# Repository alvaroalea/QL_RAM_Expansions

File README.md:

# SINCLAIR QL RAM Expansion Boards

## THIS IS THE DEVEL REPOSITORY, USE AT YOUR OWN RISK

(C) 2022-2026 Alvaro Alea Fernandez and others

If no license is specify in each folder, are under: CERN Open Hardware Licence Version 2 - Strongly Reciprocal

https://ohwr.org/cern_ohl_s_v2.txt

This reporsitory contains severals design of RAM expansion boards for the Sinclair QL, some of them area new design, and other are reverse enginiered of products seld in the 80's for the sinclair QL:

## QL_external_ram_896Kb

New design in 2026, based on qubide card of liont, https://hackaday.io/project/183490-qubide-clone-with-640k-or-704k-ram-upgrade-for-ql

Include a 1Mbyte StaticRam in a very small board with pass-through. This is the prefered design if you are new to the Sinclair QL

## qlexternal512kram_MIX

My old 2022 design, based on qubide card of Jose Leandro and work of McLeod Ideafix, using a 512Kb StaticRam in a very small board with pass-through. two of this board can be stacked to achive the 892Kb of RAM that is the maximun possible on a Sinclair QL

## QL_Internal_512Kb_SRAM

This is a clone of a model sell in ebay of a internal expansion RAM, similar to my internal 512Kb card, it fit between the 68008 and the mainboard of the QL

## QL_2560RAM_ROM

A board saw in theqlforum that include 256Kb of RAM and an chip of ROM, ideally to incorporate a ToolKit to the RAM expansion

## QL_Miracle_Trump_RAM

A board saw in theqlforum, this board include 2x256Kb of Dinamic RAM, for use with normal QL or QL with Trump Card 0Kb.

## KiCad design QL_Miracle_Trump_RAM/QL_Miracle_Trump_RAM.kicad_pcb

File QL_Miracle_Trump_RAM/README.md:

# Miracle's 256-512Kb ExpandRam board for Sinclair QL

## THIS HAS NOT BEEN TESTED, USE UNDER YOU RESPONSABILITY

(C) 2026 Alvaro Alea Fernandez

License under: CERN Open Hardware Licence Version 2 - Strongly Reciprocal

https://ohwr.org/cern_ohl_s_v2.txt

##Instructions

### COMPONENTE REQUIERED

8 or 16  41256 RAM chips 120 to 150nS SPEED.

If fitting 8 RAMS (256K) the row closest to the edge connector should be used.

Pin One of the RAM chips is furthest from above edge connector.

CARE ELECTRONICS

800 St Albans RD

GARSTON

WATFORD

HERTS        TEL 0923 672102

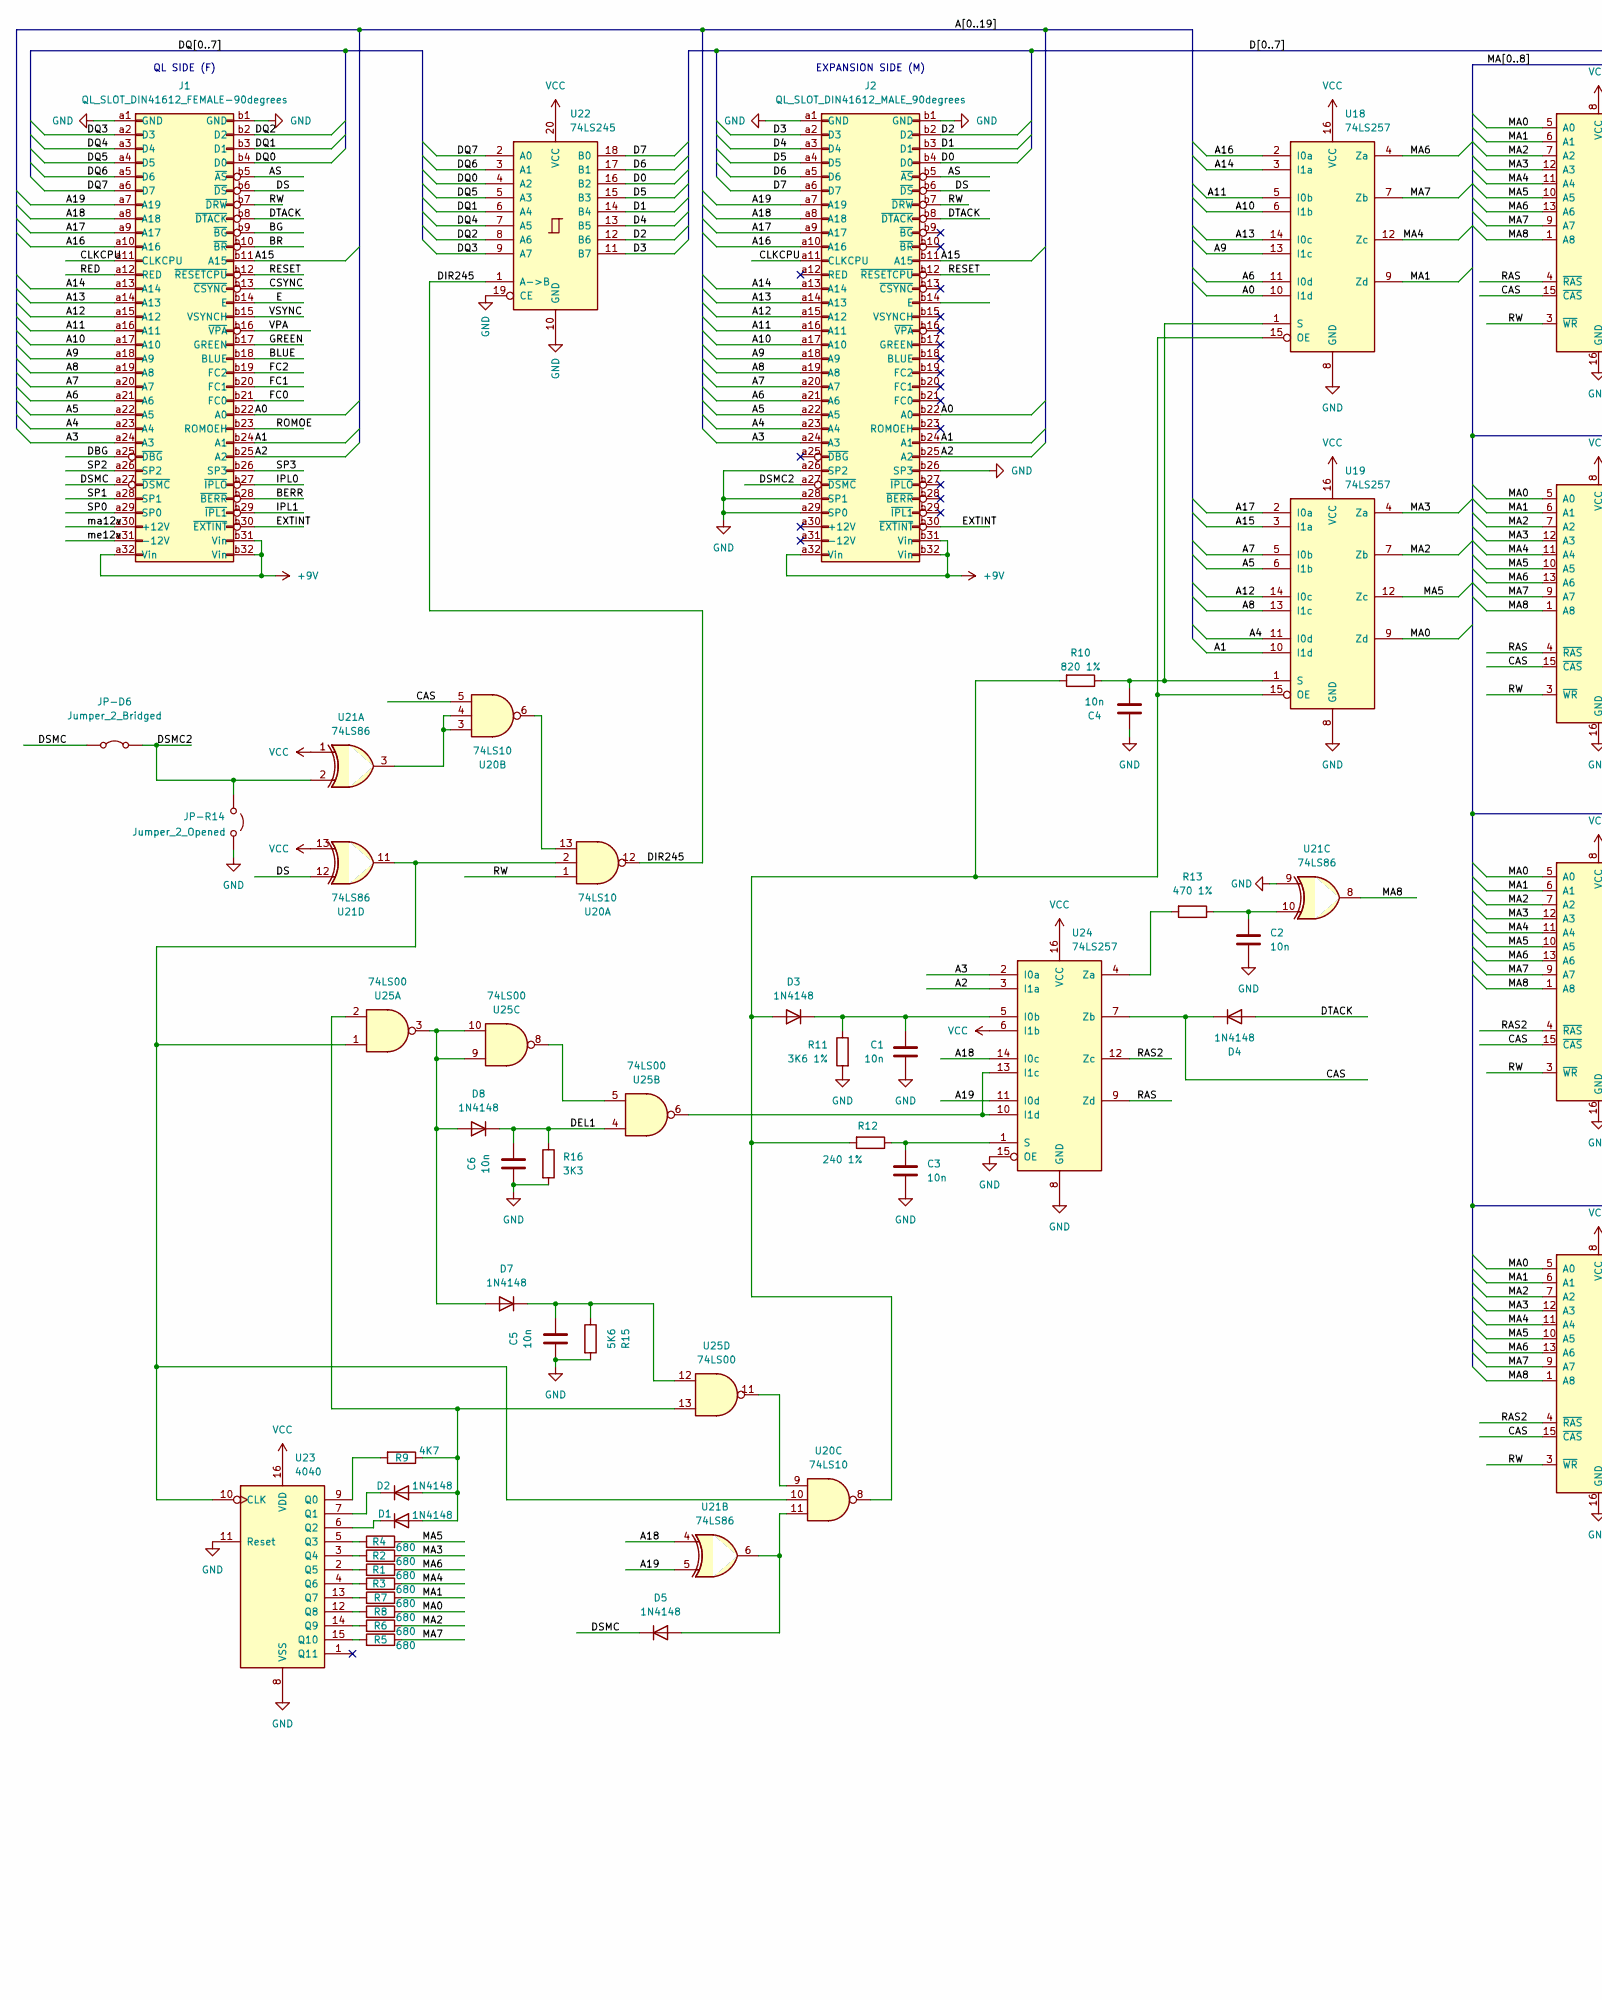
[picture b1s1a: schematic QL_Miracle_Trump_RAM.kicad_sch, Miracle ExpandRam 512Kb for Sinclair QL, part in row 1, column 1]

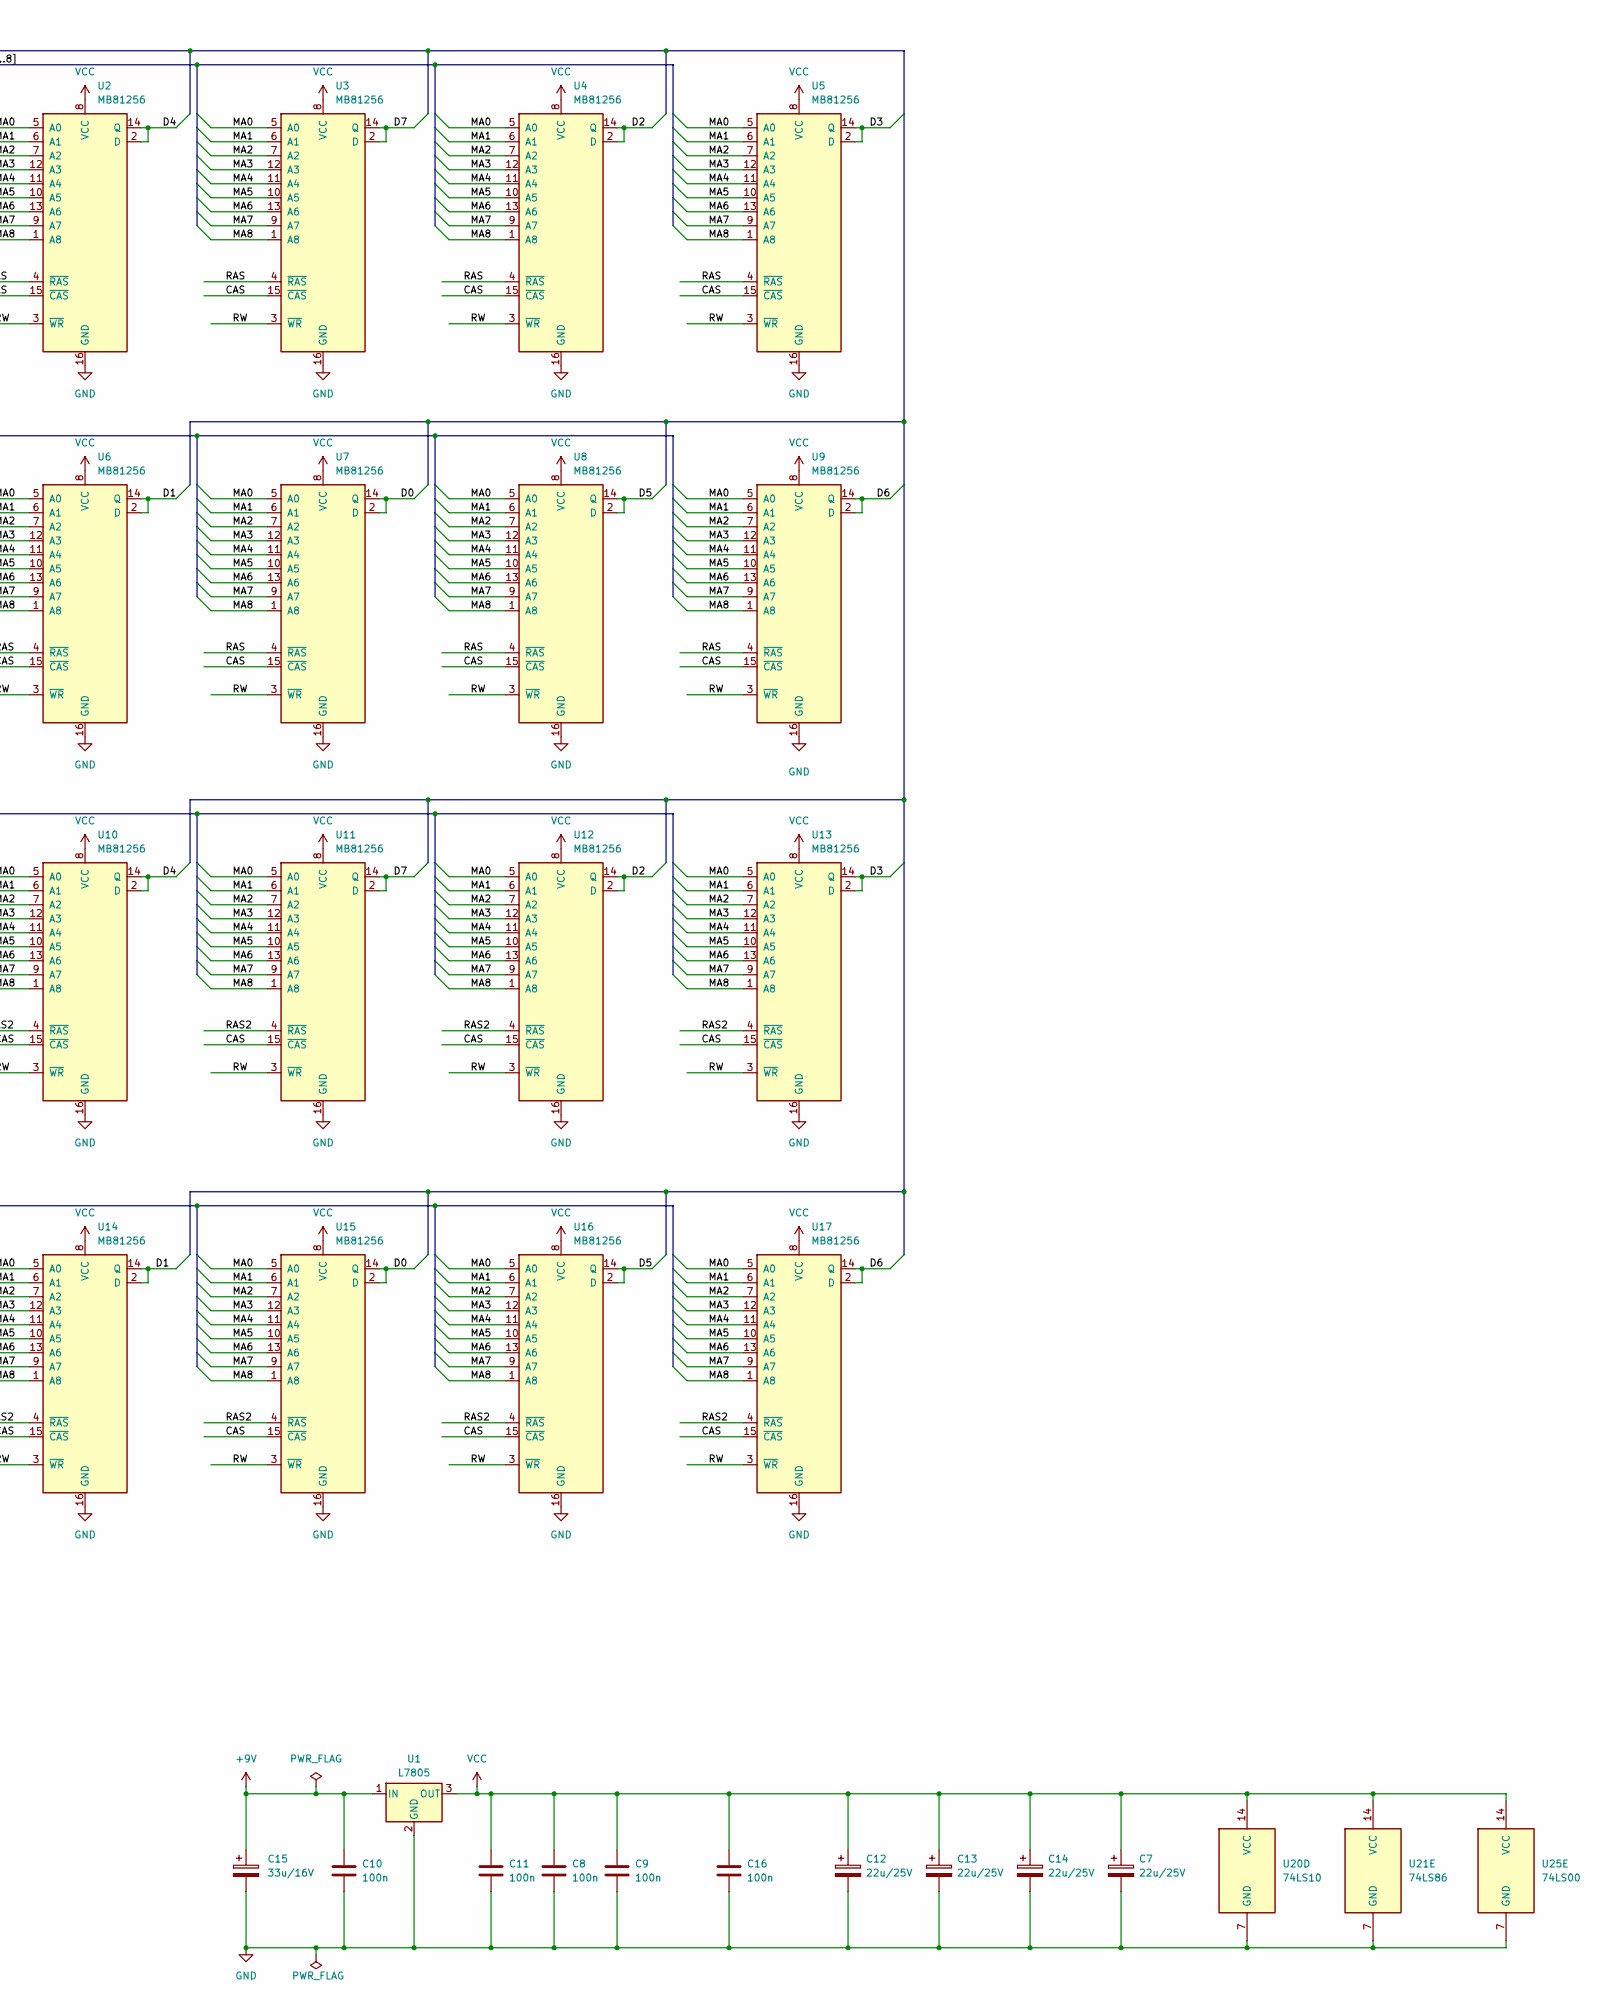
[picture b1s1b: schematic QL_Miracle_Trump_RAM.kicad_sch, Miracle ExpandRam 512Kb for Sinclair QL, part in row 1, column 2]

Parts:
C1, C2, C3, C4, C5, C6: 10n; C_Disc_D4.3mm_W1.9mm_P5.00mm
C7, C12, C13, C14: 22u/25V; CP_Radial_D8.0mm_P5.00mm
C8, C9, C10, C11, C16: 100n; C_Disc_D4.3mm_W1.9mm_P5.00mm
C15: 33u/16V; CP_Axial_L11.0mm_D5.0mm_P18.00mm_Horizontal
D1, D2, D3, D4, D5, D7, D8: 1N4148; D_DO-35_SOD27_P10.16mm_Horizontal
J1: QL_SLOT_DIN41612_FEMALE-90degrees; DIN41612_B_2x32_Female_Horizontal_THT
J2: QL_SLOT_DIN41612_MALE_90degrees; DIN41612_B_2x32_Male_Horizontal_THT
JP-D6: Jumper_2_Bridged; Jumper_P10.16mm_Horizontal
JP-R14: Jumper_2_Opened; Jumper_P10.16mm_Horizontal
R1, R2, R3, R4, R5, R6, R7, R8: 680; R_Axial_DIN0207_L6.3mm_D2.5mm_P10.16mm_Horizontal
R9: 4K7; R_Axial_DIN0207_L6.3mm_D2.5mm_P10.16mm_Horizontal
R10: 820 1%; R_Axial_DIN0207_L6.3mm_D2.5mm_P10.16mm_Horizontal
R11: 3K6 1%; R_Axial_DIN0207_L6.3mm_D2.5mm_P10.16mm_Horizontal
R12: 240 1%; R_Axial_DIN0207_L6.3mm_D2.5mm_P10.16mm_Horizontal
R13: 470 1%; R_Axial_DIN0207_L6.3mm_D2.5mm_P10.16mm_Horizontal
R15: 5K6; R_Axial_DIN0207_L6.3mm_D2.5mm_P10.16mm_Horizontal
R16: 3K3; R_Axial_DIN0207_L6.3mm_D2.5mm_P10.16mm_Horizontal
U1: L7805; TO-220-3_Horizontal_TabDown
U2, U3, U4, U5, U6, U7, U8, U9, U10, U11, U12, U13, U14, U15, U16, U17: MB81256; DIP-16_W7.62mm
U18, U19, U24: 74LS257; DIP-16_W7.62mm
U20: 74LS10; DIP-14_W7.62mm
U21: 74LS86; DIP-14_W7.62mm
U22: 74LS245; DIP-20_W7.62mm
U23: 4040; DIP-16_W7.62mm
U25: 74LS00; DIP-14_W7.62mm

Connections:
+9V: C10.1, C15.1, J1.a32 (Vin), J1.b31 (Vin), J1.b32 (Vin), J2.a32 (Vin), J2.b31 (Vin), J2.b32 (Vin), U1.1 (IN)
/A0: J1.b22 (A0), J2.b22 (A0), U18.10 (I1d)
/A1: J1.b24 (A1), J2.b24 (A1), U19.10 (I1d)
/A2: J1.b25 (A2), J2.b25 (A2), U24.3 (I1a)
/A3: J1.a24 (A3), J2.a24 (A3), U24.2 (I0a)
/A4: J1.a23 (A4), J2.a23 (A4), U19.11 (I0d)
/A5: J1.a22 (A5), J2.a22 (A5), U19.6 (I1b)
/A6: J1.a21 (A6), J2.a21 (A6), U18.11 (I0d)
/A7: J1.a20 (A7), J2.a20 (A7), U19.5 (I0b)
/A8: J1.a19 (A8), J2.a19 (A8), U19.13 (I1c)
/A9: J1.a18 (A9), J2.a18 (A9), U18.13 (I1c)
/A10: J1.a17 (A10), J2.a17 (A10), U18.6 (I1b)
/A11: J1.a16 (A11), J2.a16 (A11), U18.5 (I0b)
/A12: J1.a15 (A12), J2.a15 (A12), U19.14 (I0c)
/A13: J1.a14 (A13), J2.a14 (A13), U18.14 (I0c)
/A14: J1.a13 (A14), J2.a13 (A14), U18.3 (I1a)
/A15: J1.b11 (A15), J2.b11 (A15), U19.3 (I1a)
/A16: J1.a10 (A16), J2.a10 (A16), U18.2 (I0a)
/A17: J1.a9 (A17), J2.a9 (A17), U19.2 (I0a)
/A18: J1.a8 (A18), J2.a8 (A18), U21.4, U24.14 (I0c)
/A19: J1.a7 (A19), J2.a7 (A19), U21.5, U24.11 (I0d)
/AS: J1.b5 (~AS), J2.b5 (~AS)
/BERR: J1.b28 (~BERR)
/BG: J1.b9 (~BG)
/BLUE: J1.b18 (BLUE)
/BR: J1.b10 (~BR)
/CAS: D4.1 (K), U2.15 (~CAS), U3.15 (~CAS), U4.15 (~CAS), U5.15 (~CAS), U6.15 (~CAS), U7.15 (~CAS), U8.15 (~CAS), U9.15 (~CAS), U10.15 (~CAS), U11.15 (~CAS), U12.15 (~CAS), U13.15 (~CAS), U14.15 (~CAS), U15.15 (~CAS), U16.15 (~CAS), U17.15 (~CAS), U20.5, U24.7 (Zb)
/CLKCPU: J1.a11 (CLKCPU), J2.a11 (CLKCPU)
/CSYNC: J1.b13 (~CSYNC)
/D0: J2.b4 (D0), U7.2 (D), U7.14 (Q), U15.2 (D), U15.14 (Q), U22.16 (B2)
/D1: J2.b3 (D1), U6.2 (D), U6.14 (Q), U14.2 (D), U14.14 (Q), U22.14 (B4)
/D2: J2.b2 (D2), U4.2 (D), U4.14 (Q), U12.2 (D), U12.14 (Q), U22.12 (B6)
/D3: J2.a2 (D3), U5.2 (D), U5.14 (Q), U13.2 (D), U13.14 (Q), U22.11 (B7)
/D4: J2.a3 (D4), U2.2 (D), U2.14 (Q), U10.2 (D), U10.14 (Q), U22.13 (B5)
/D5: J2.a4 (D5), U8.2 (D), U8.14 (Q), U16.2 (D), U16.14 (Q), U22.15 (B3)
/D6: J2.a5 (D6), U9.2 (D), U9.14 (Q), U17.2 (D), U17.14 (Q), U22.17 (B1)
/D7: J2.a6 (D7), U3.2 (D), U3.14 (Q), U11.2 (D), U11.14 (Q), U22.18 (B0)
/DBG: J1.a25 (~DBG)
/DEL1: C6.1, D8.1 (K), R16.1, U25.4
/DIR245: U20.12, U22.1 (A->B)
/DQ0: J1.b4 (D0), U22.4 (A2)
/DQ1: J1.b3 (D1), U22.6 (A4)
/DQ2: J1.b2 (D2), U22.8 (A6)
/DQ3: J1.a2 (D3), U22.9 (A7)
/DQ4: J1.a3 (D4), U22.7 (A5)
/DQ5: J1.a4 (D5), U22.5 (A3)
/DQ6: J1.a5 (D6), U22.3 (A1)
/DQ7: J1.a6 (D7), U22.2 (A0)
/DS: J1.b6 (~DS), J2.b6 (~DS), U21.12
/DSMC: D5.1 (K), J1.a27 (~DSMC), JP-D6.1 (A)
/DSMC2: J2.a27 (~DSMC), JP-D6.2 (B), JP-R14.1 (A), U21.2
/DTACK: D4.2 (A), J1.b8 (~DTACK), J2.b8 (~DTACK)
/E: J1.b14 (E)
/EXTINT: J1.b30 (~EXTINT), J2.b30 (~EXTINT)
/FC0: J1.b21 (FC0)
/FC1: J1.b20 (FC1)
/FC2: J1.b19 (FC2)
/GREEN: J1.b17 (GREEN)
/IPL0: J1.b27 (~IPLO)
/IPL1: J1.b29 (~IPL1)
/MA0: R8.1, U2.5 (A0), U3.5 (A0), U4.5 (A0), U5.5 (A0), U6.5 (A0), U7.5 (A0), U8.5 (A0), U9.5 (A0), U10.5 (A0), U11.5 (A0), U12.5 (A0), U13.5 (A0), U14.5 (A0), U15.5 (A0), U16.5 (A0), U17.5 (A0), U19.9 (Zd)
/MA1: R7.1, U2.6 (A1), U3.6 (A1), U4.6 (A1), U5.6 (A1), U6.6 (A1), U7.6 (A1), U8.6 (A1), U9.6 (A1), U10.6 (A1), U11.6 (A1), U12.6 (A1), U13.6 (A1), U14.6 (A1), U15.6 (A1), U16.6 (A1), U17.6 (A1), U18.9 (Zd)
/MA2: R6.1, U2.7 (A2), U3.7 (A2), U4.7 (A2), U5.7 (A2), U6.7 (A2), U7.7 (A2), U8.7 (A2), U9.7 (A2), U10.7 (A2), U11.7 (A2), U12.7 (A2), U13.7 (A2), U14.7 (A2), U15.7 (A2), U16.7 (A2), U17.7 (A2), U19.7 (Zb)
/MA3: R2.1, U2.12 (A3), U3.12 (A3), U4.12 (A3), U5.12 (A3), U6.12 (A3), U7.12 (A3), U8.12 (A3), U9.12 (A3), U10.12 (A3), U11.12 (A3), U12.12 (A3), U13.12 (A3), U14.12 (A3), U15.12 (A3), U16.12 (A3), U17.12 (A3), U19.4 (Za)
/MA4: R3.1, U2.11 (A4), U3.11 (A4), U4.11 (A4), U5.11 (A4), U6.11 (A4), U7.11 (A4), U8.11 (A4), U9.11 (A4), U10.11 (A4), U11.11 (A4), U12.11 (A4), U13.11 (A4), U14.11 (A4), U15.11 (A4), U16.11 (A4), U17.11 (A4), U18.12 (Zc)
/MA5: R4.1, U2.10 (A5), U3.10 (A5), U4.10 (A5), U5.10 (A5), U6.10 (A5), U7.10 (A5), U8.10 (A5), U9.10 (A5), U10.10 (A5), U11.10 (A5), U12.10 (A5), U13.10 (A5), U14.10 (A5), U15.10 (A5), U16.10 (A5), U17.10 (A5), U19.12 (Zc)
/MA6: R1.1, U2.13 (A6), U3.13 (A6), U4.13 (A6), U5.13 (A6), U6.13 (A6), U7.13 (A6), U8.13 (A6), U9.13 (A6), U10.13 (A6), U11.13 (A6), U12.13 (A6), U13.13 (A6), U14.13 (A6), U15.13 (A6), U16.13 (A6), U17.13 (A6), U18.4 (Za)
/MA7: R5.1, U2.9 (A7), U3.9 (A7), U4.9 (A7), U5.9 (A7), U6.9 (A7), U7.9 (A7), U8.9 (A7), U9.9 (A7), U10.9 (A7), U11.9 (A7), U12.9 (A7), U13.9 (A7), U14.9 (A7), U15.9 (A7), U16.9 (A7), U17.9 (A7), U18.7 (Zb)
/MA8: U2.1 (A8), U3.1 (A8), U4.1 (A8), U5.1 (A8), U6.1 (A8), U7.1 (A8), U8.1 (A8), U9.1 (A8), U10.1 (A8), U11.1 (A8), U12.1 (A8), U13.1 (A8), U14.1 (A8), U15.1 (A8), U16.1 (A8), U17.1 (A8), U21.8
/RAS: U2.4 (~RAS), U3.4 (~RAS), U4.4 (~RAS), U5.4 (~RAS), U6.4 (~RAS), U7.4 (~RAS), U8.4 (~RAS), U9.4 (~RAS), U24.9 (Zd)
/RAS2: U10.4 (~RAS), U11.4 (~RAS), U12.4 (~RAS), U13.4 (~RAS), U14.4 (~RAS), U15.4 (~RAS), U16.4 (~RAS), U17.4 (~RAS), U24.12 (Zc)
/RED: J1.a12 (RED)
/RESET: J1.b12 (~RESETCPU), J2.b12 (~RESETCPU)
/ROMOE: J1.b23 (ROMOEH)
/RW: J1.b7 (~DRW), J2.b7 (~DRW), U2.3 (~WR), U3.3 (~WR), U4.3 (~WR), U5.3 (~WR), U6.3 (~WR), U7.3 (~WR), U8.3 (~WR), U9.3 (~WR), U10.3 (~WR), U11.3 (~WR), U12.3 (~WR), U13.3 (~WR), U14.3 (~WR), U15.3 (~WR), U16.3 (~WR), U17.3 (~WR), U20.1
/SP0: J1.a29 (SP0)
/SP1: J1.a28 (SP1)
/SP2: J1.a26 (SP2)
/SP3: J1.b26 (SP3)
/VPA: J1.b16 (~VPA)
/VSYNC: J1.b15 (VSYNCH)
/ma12v: J1.a30 (+12V)
/me12v: J1.a31 (-12V)
GND: C1.2, C2.2, C3.1, C4.2, C5.2, C6.2, C7.2, C8.2, C9.2, C10.2, C11.2, C12.2, C13.2, C14.2, C15.2, C16.2, J1.a1 (GND), J1.b1 (GND), J2.a1 (GND), J2.a26 (SP2), J2.a28 (SP1), J2.a29 (SP0), J2.b1 (GND), J2.b26 (SP3), JP-R14.2 (B), R11.2, R15.2, R16.2, U1.2 (GND), U2.16 (GND), U3.16 (GND), U4.16 (GND), U5.16 (GND), U6.16 (GND), U7.16 (GND), U8.16 (GND), U9.16 (GND), U10.16 (GND), U11.16 (GND), U12.16 (GND), U13.16 (GND), U14.16 (GND), U15.16 (GND), U16.16 (GND), U17.16 (GND), U18.8 (GND), U19.8 (GND), U20.7 (GND), U21.7 (GND), U21.9, U22.10 (GND), U22.19 (CE), U23.8 (VSS), U23.11 (Reset), U24.8 (GND), U24.15 (OE), U25.7 (GND)
unnamed: C2.1, R13.1, U21.10
unnamed: D1.2 (A), D2.2 (A), R9.1, U25.2, U25.13
unnamed: D1.1 (K), U23.6 (Q2)
unnamed: D2.1 (K), U23.7 (Q1)
unnamed: D3.2 (A), R10.2, R12.2, U18.15 (OE), U19.15 (OE), U20.8
unnamed: C1.1, D3.1 (K), R11.1, U24.5 (I0b)
unnamed: D5.2 (A), U20.11, U21.6
unnamed: D7.2 (A), D8.2 (A), U25.3, U25.9, U25.10
unnamed: C5.1, D7.1 (K), R15.1, U25.12
unnamed: C4.1, R10.1, U18.1 (S), U19.1 (S)
unnamed: U20.3, U20.4, U21.3
unnamed: U20.9, U25.11
unnamed: U20.6, U20.13
unnamed: U20.2, U20.10, U21.11, U23.10 (CLK), U25.1
unnamed: R9.2, U23.9 (Q0)
unnamed: R4.2, U23.5 (Q3)
unnamed: R2.2, U23.3 (Q4)
unnamed: R1.2, U23.2 (Q5)
unnamed: R3.2, U23.4 (Q6)
unnamed: R7.2, U23.13 (Q7)
unnamed: R8.2, U23.12 (Q8)
unnamed: R6.2, U23.14 (Q9)
unnamed: R5.2, U23.15 (Q10)
unnamed: U24.10 (I1d), U24.13 (I1c), U25.6
unnamed: C3.2, R12.1, U24.1 (S)
unnamed: R13.2, U24.4 (Za)
unnamed: U25.5, U25.8
VCC: C7.1, C8.1, C9.1, C11.1, C12.1, C13.1, C14.1, C16.1, U1.3 (OUT), U2.8 (VCC), U3.8 (VCC), U4.8 (VCC), U5.8 (VCC), U6.8 (VCC), U7.8 (VCC), U8.8 (VCC), U9.8 (VCC), U10.8 (VCC), U11.8 (VCC), U12.8 (VCC), U13.8 (VCC), U14.8 (VCC), U15.8 (VCC), U16.8 (VCC), U17.8 (VCC), U18.16 (VCC), U19.16 (VCC), U20.14 (VCC), U21.1, U21.13, U21.14 (VCC), U22.20 (VCC), U23.16 (VDD), U24.6 (I1b), U24.16 (VCC), U25.14 (VCC)

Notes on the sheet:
EXPANSION SIDE (M)
QL SIDE (F)

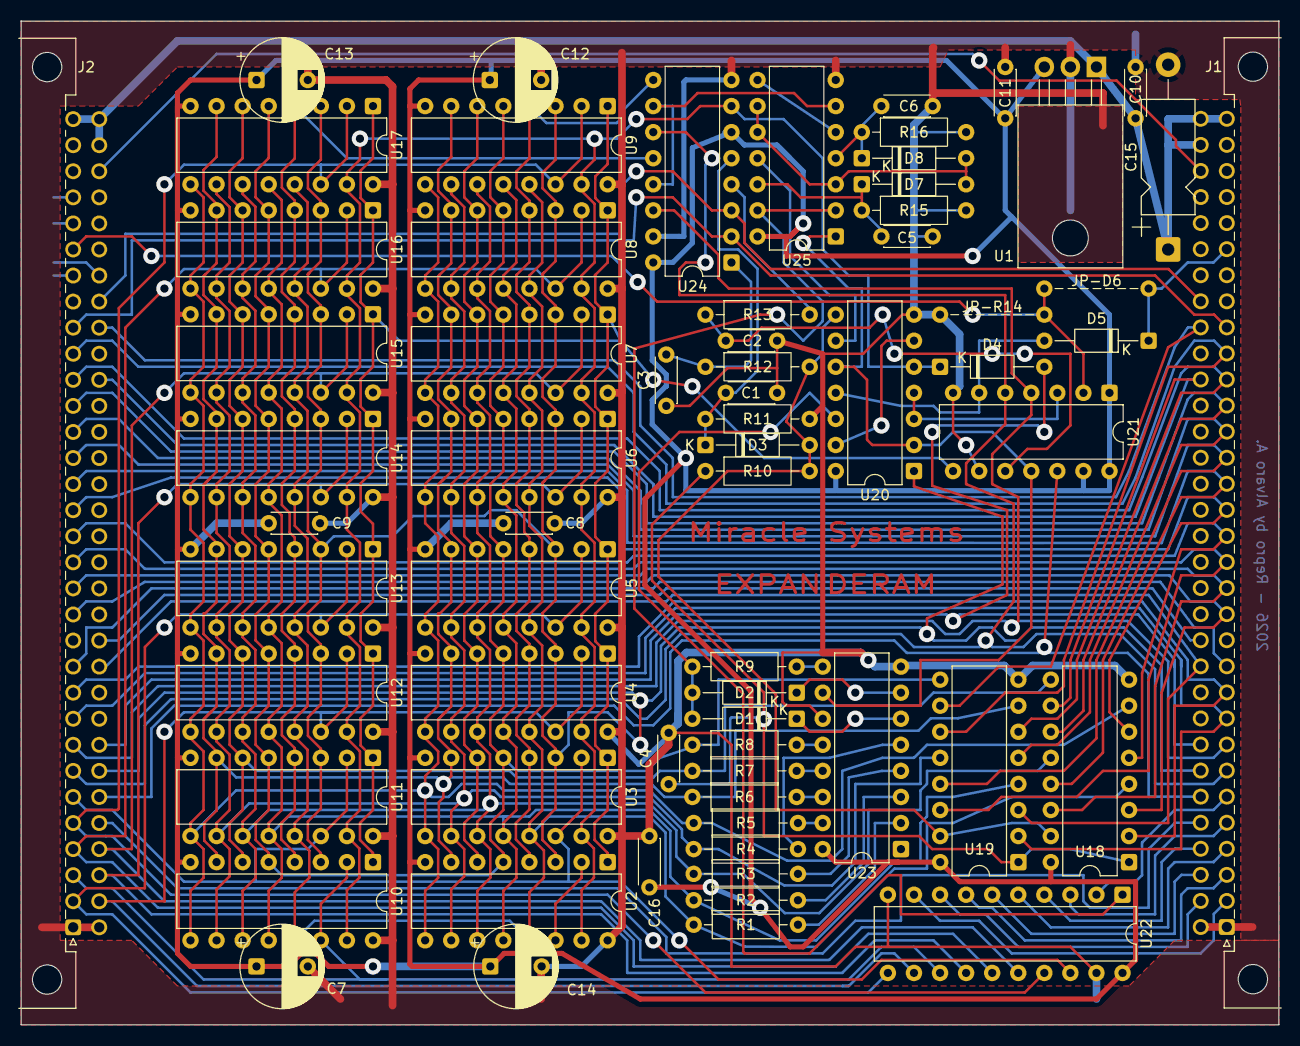
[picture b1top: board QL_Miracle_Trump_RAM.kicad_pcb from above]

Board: 2 copper layers, 122.6 x 97.8 mm, 67 parts (0 on the bottom side), 89 nets.

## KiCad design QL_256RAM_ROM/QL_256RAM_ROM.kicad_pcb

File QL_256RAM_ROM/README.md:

# RAM/ROM Sinclair QL Interface.
A board that provide 256Kb of RAM and a Toolkit in ROM for the Sinclair QL.

# THIS IS WORK IN PROGRESS.ACTUALY THIS INTERFACE DO NOT WORK!!!!! BE AWARE
## NOT FOR USE, THIS IS ONLY A MOCKUP, WORK IN PROGRESS

(C) 2023 Alvaro Alea Fernandez.

This board has been reversed engineered from pictures by vanpeebles in this post: https://qlforum.co.uk/viewtopic.php?t=4353

Some Render of the board:

The original pictures:

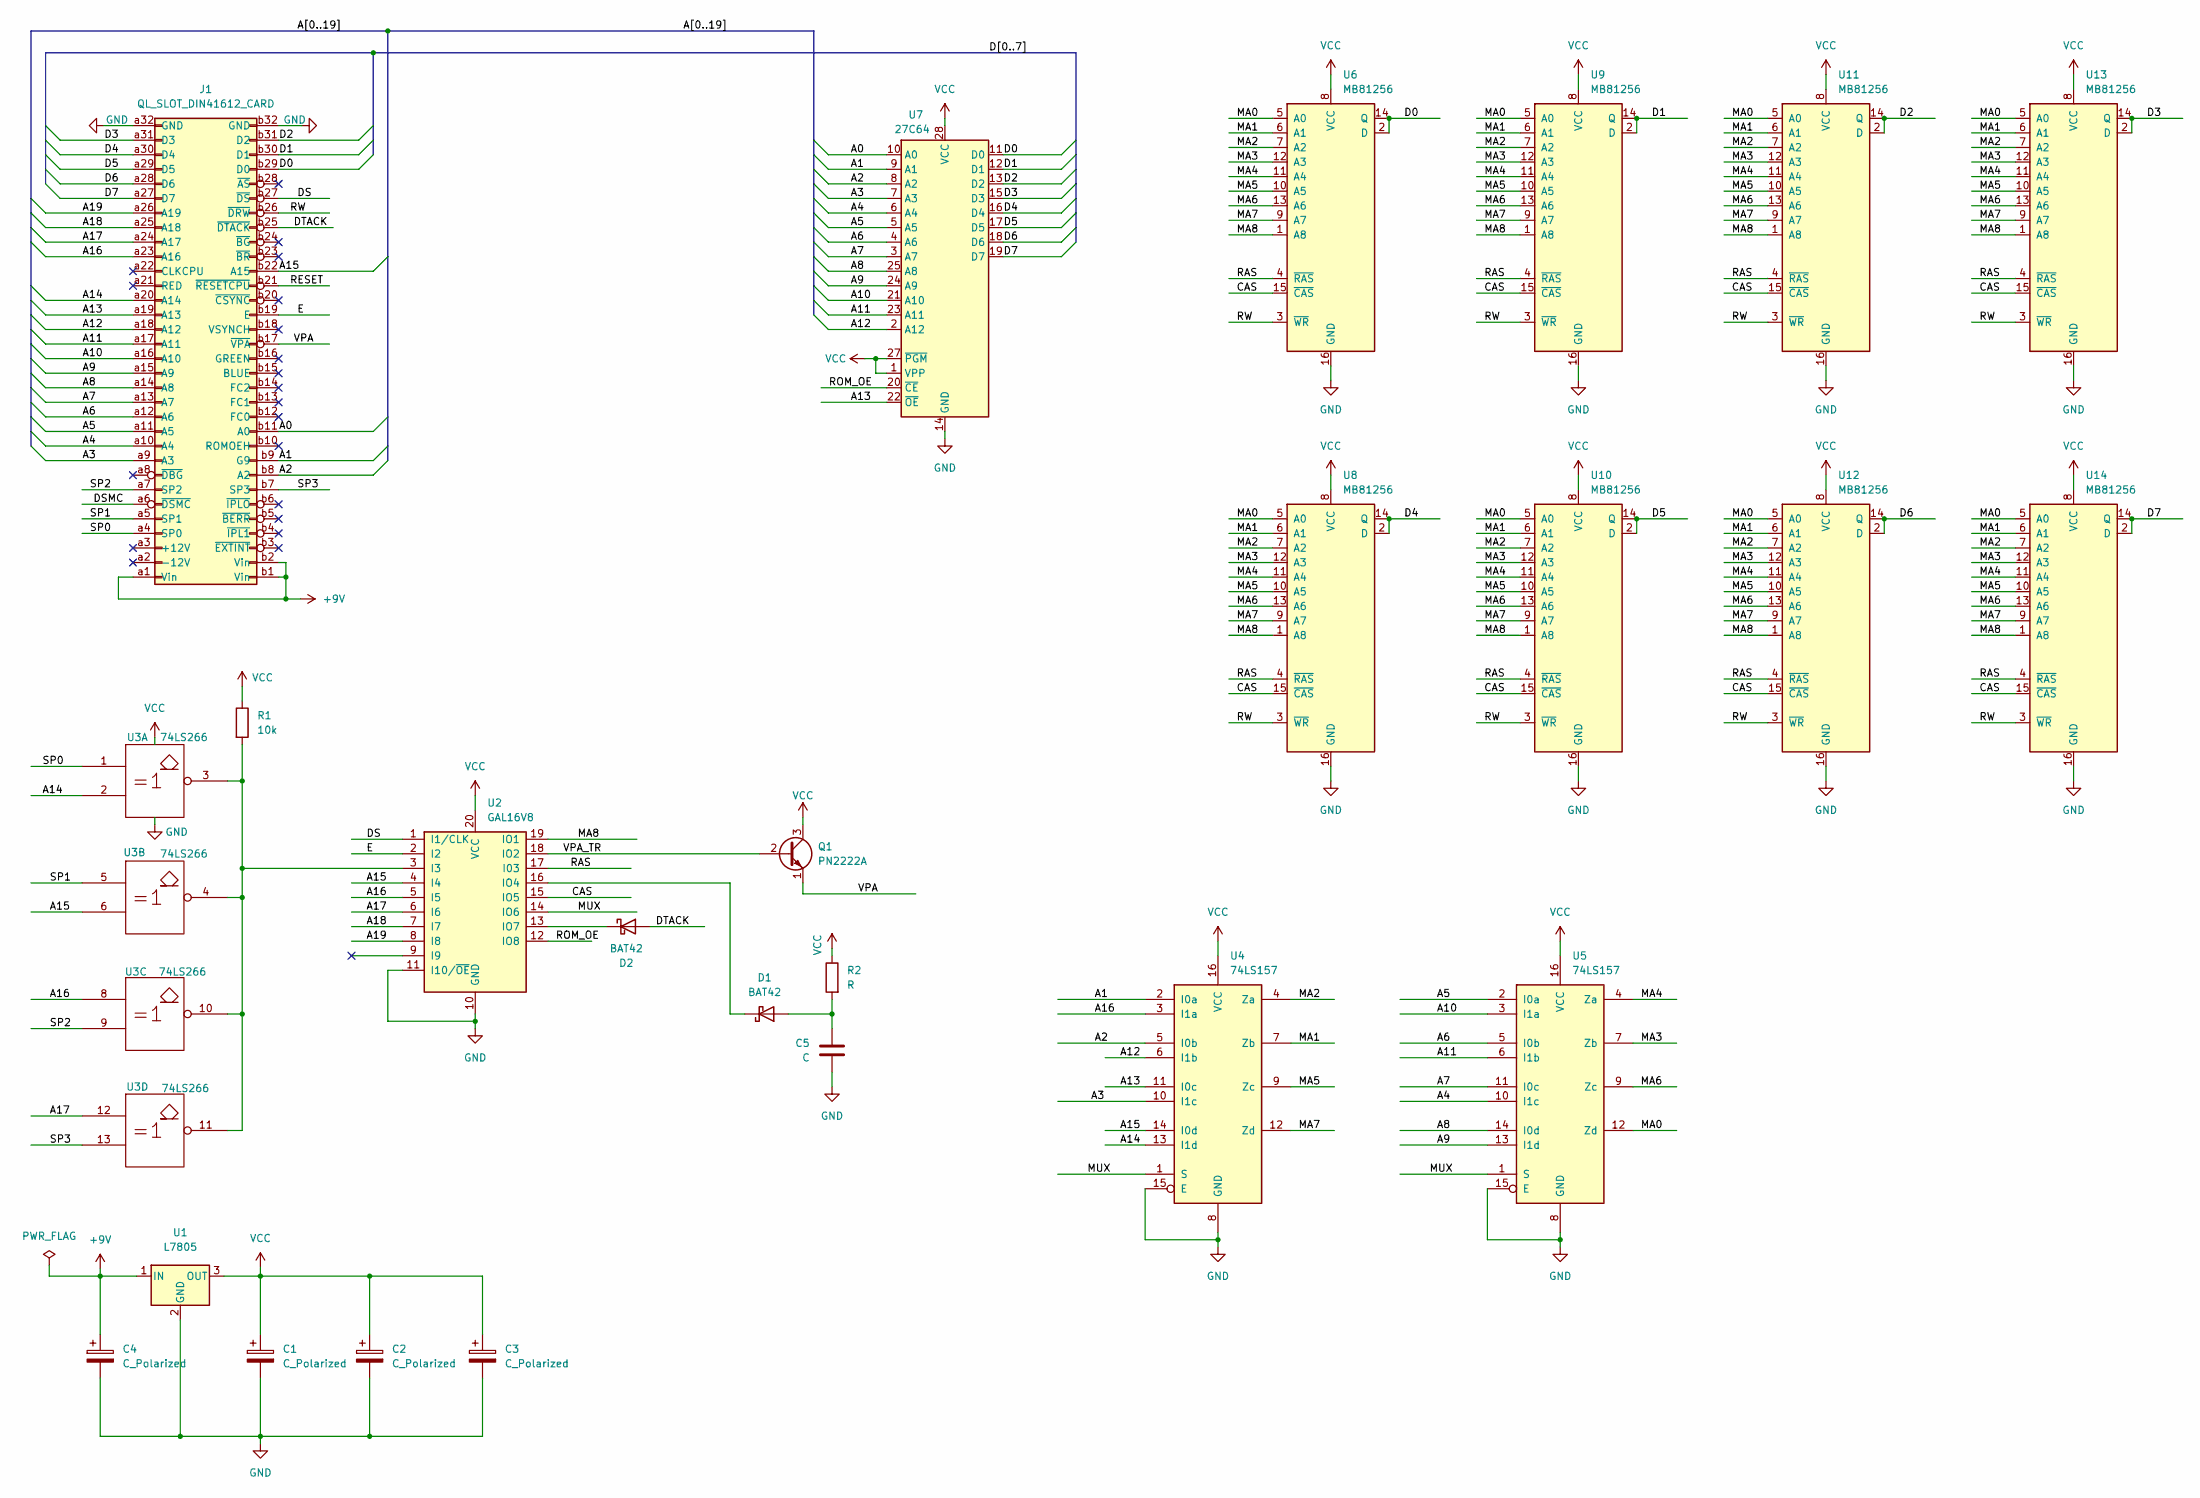
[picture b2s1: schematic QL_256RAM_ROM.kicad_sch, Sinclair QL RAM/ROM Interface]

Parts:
C1, C2, C3: C_Polarized; CP_Radial_D6.3mm_P2.50mm
C4: C_Polarized; CP_Axial_L10.0mm_D4.5mm_P15.00mm_Horizontal
C5: C; C_Disc_D5.1mm_W3.2mm_P5.00mm
D1, D2: BAT42; D_DO-35_SOD27_P7.62mm_Horizontal
J1: QL_SLOT_DIN41612_CARD; DIN41612_B_2x32_Male_Horizontal_THT
Q1: PN2222A; TO-92_Inline
R1: 10k; R_Axial_DIN0207_L6.3mm_D2.5mm_P10.16mm_Horizontal
R2: R; R_Axial_DIN0207_L6.3mm_D2.5mm_P2.54mm_Vertical
U1: L7805; TO-220-3_Horizontal_TabDown
U2: GAL16V8; DIP-20_W7.62mm_LongPads
U3: 74LS266; DIP-14_W7.62mm_LongPads
U4, U5: 74LS157; DIP-16_W7.62mm_LongPads
U6, U8, U9, U10, U11, U12, U13, U14: MB81256; DIP-16_W7.62mm_LongPads
U7: 27C64; DIP-28_W15.24mm_LongPads

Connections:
+9V: C4.1, J1.a1 (Vin), J1.b1 (Vin), J1.b2 (Vin), U1.1 (IN)
/A0: J1.b11 (A0), U7.10 (A0)
/A1: J1.b9 (G9), U4.2 (I0a), U7.9 (A1)
/A2: J1.b8 (A2), U4.5 (I0b), U7.8 (A2)
/A3: J1.a9 (A3), U4.10 (I1c), U7.7 (A3)
/A4: J1.a10 (A4), U5.10 (I1c), U7.6 (A4)
/A5: J1.a11 (A5), U5.2 (I0a), U7.5 (A5)
/A6: J1.a12 (A6), U5.5 (I0b), U7.4 (A6)
/A7: J1.a13 (A7), U5.11 (I0c), U7.3 (A7)
/A8: J1.a14 (A8), U5.14 (I0d), U7.25 (A8)
/A9: J1.a15 (A9), U5.13 (I1d), U7.24 (A9)
/A10: J1.a16 (A10), U5.3 (I1a), U7.21 (A10)
/A11: J1.a17 (A11), U5.6 (I1b), U7.23 (A11)
/A12: J1.a18 (A12), U4.6 (I1b), U7.2 (A12)
/A13: J1.a19 (A13), U4.11 (I0c), U7.22 (~OE)
/A14: J1.a20 (A14), U3.2, U4.13 (I1d)
/A15: J1.b22 (A15), U2.4 (I4), U3.6, U4.14 (I0d)
/A16: J1.a23 (A16), U2.5 (I5), U3.8, U4.3 (I1a)
/A17: J1.a24 (A17), U2.6 (I6), U3.12
/A18: J1.a25 (A18), U2.7 (I7)
/A19: J1.a26 (A19), U2.8 (I8)
/CAS: U2.15 (IO5), U6.15 (~CAS), U8.15 (~CAS), U9.15 (~CAS), U10.15 (~CAS), U11.15 (~CAS), U12.15 (~CAS), U13.15 (~CAS), U14.15 (~CAS)
/D0: J1.b29 (D0), U6.2 (D), U6.14 (Q), U7.11 (D0)
/D1: J1.b30 (D1), U7.12 (D1), U9.2 (D), U9.14 (Q)
/D2: J1.b31 (D2), U7.13 (D2), U11.2 (D), U11.14 (Q)
/D3: J1.a31 (D3), U7.15 (D3), U13.2 (D), U13.14 (Q)
/D4: J1.a30 (D4), U7.16 (D4), U8.2 (D), U8.14 (Q)
/D5: J1.a29 (D5), U7.17 (D5), U10.2 (D), U10.14 (Q)
/D6: J1.a28 (D6), U7.18 (D6), U12.2 (D), U12.14 (Q)
/D7: J1.a27 (D7), U7.19 (D7), U14.2 (D), U14.14 (Q)
/DS: J1.b27 (~DS), U2.1 (I1/CLK)
/DSMC: J1.a6 (~DSMC)
/DTACK: D2.2 (A), J1.b25 (~DTACK)
/E: J1.b19 (E), U2.2 (I2)
/MA0: U5.12 (Zd), U6.5 (A0), U8.5 (A0), U9.5 (A0), U10.5 (A0), U11.5 (A0), U12.5 (A0), U13.5 (A0), U14.5 (A0)
/MA1: U4.7 (Zb), U6.6 (A1), U8.6 (A1), U9.6 (A1), U10.6 (A1), U11.6 (A1), U12.6 (A1), U13.6 (A1), U14.6 (A1)
/MA2: U4.4 (Za), U6.7 (A2), U8.7 (A2), U9.7 (A2), U10.7 (A2), U11.7 (A2), U12.7 (A2), U13.7 (A2), U14.7 (A2)
/MA3: U5.7 (Zb), U6.12 (A3), U8.12 (A3), U9.12 (A3), U10.12 (A3), U11.12 (A3), U12.12 (A3), U13.12 (A3), U14.12 (A3)
/MA4: U5.4 (Za), U6.11 (A4), U8.11 (A4), U9.11 (A4), U10.11 (A4), U11.11 (A4), U12.11 (A4), U13.11 (A4), U14.11 (A4)
/MA5: U4.9 (Zc), U6.10 (A5), U8.10 (A5), U9.10 (A5), U10.10 (A5), U11.10 (A5), U12.10 (A5), U13.10 (A5), U14.10 (A5)
/MA6: U5.9 (Zc), U6.13 (A6), U8.13 (A6), U9.13 (A6), U10.13 (A6), U11.13 (A6), U12.13 (A6), U13.13 (A6), U14.13 (A6)
/MA7: U4.12 (Zd), U6.9 (A7), U8.9 (A7), U9.9 (A7), U10.9 (A7), U11.9 (A7), U12.9 (A7), U13.9 (A7), U14.9 (A7)
/MA8: U2.19 (IO1), U6.1 (A8), U8.1 (A8), U9.1 (A8), U10.1 (A8), U11.1 (A8), U12.1 (A8), U13.1 (A8), U14.1 (A8)
/MUX: U2.14 (IO6), U4.1 (S), U5.1 (S)
/RAS: U2.17 (I03), U6.4 (~RAS), U8.4 (~RAS), U9.4 (~RAS), U10.4 (~RAS), U11.4 (~RAS), U12.4 (~RAS), U13.4 (~RAS), U14.4 (~RAS)
/RESET: J1.b21 (~RESETCPU)
/ROM_OE: U2.12 (IO8), U7.20 (~CE)
/RW: J1.b26 (~DRW), U6.3 (~WR), U8.3 (~WR), U9.3 (~WR), U10.3 (~WR), U11.3 (~WR), U12.3 (~WR), U13.3 (~WR), U14.3 (~WR)
/SP0: J1.a4 (SP0), U3.1
/SP1: J1.a5 (SP1), U3.5
/SP2: J1.a7 (SP2), U3.9
/SP3: J1.b7 (SP3), U3.13
/VPA: J1.b17 (~VPA), Q1.1 (E)
/VPA_TR: Q1.2 (B), U2.18 (IO2)
GND: C1.2, C2.2, C3.2, C4.2, C5.2, J1.a32 (GND), J1.b32 (GND), U1.2 (GND), U2.10 (GND), U2.11 (I10/~OE), U3.7 (GND), U4.8 (GND), U4.15 (E), U5.8 (GND), U5.15 (E), U6.16 (GND), U7.14 (GND), U8.16 (GND), U9.16 (GND), U10.16 (GND), U11.16 (GND), U12.16 (GND), U13.16 (GND), U14.16 (GND)
unnamed: C5.1, D1.2 (A), R2.2
unnamed: D1.1 (K), U2.16 (IO4)
unnamed: D2.1 (K), U2.13 (IO7)
unnamed: R1.2, U2.3 (I3), U3.3, U3.4, U3.10, U3.11
VCC: C1.1, C2.1, C3.1, Q1.3 (C), R1.1, R2.1, U1.3 (OUT), U2.20 (VCC), U3.14 (VCC), U4.16 (VCC), U5.16 (VCC), U6.8 (VCC), U7.1 (VPP), U7.27 (~PGM), U7.28 (VCC), U8.8 (VCC), U9.8 (VCC), U10.8 (VCC), U11.8 (VCC), U12.8 (VCC), U13.8 (VCC), U14.8 (VCC)

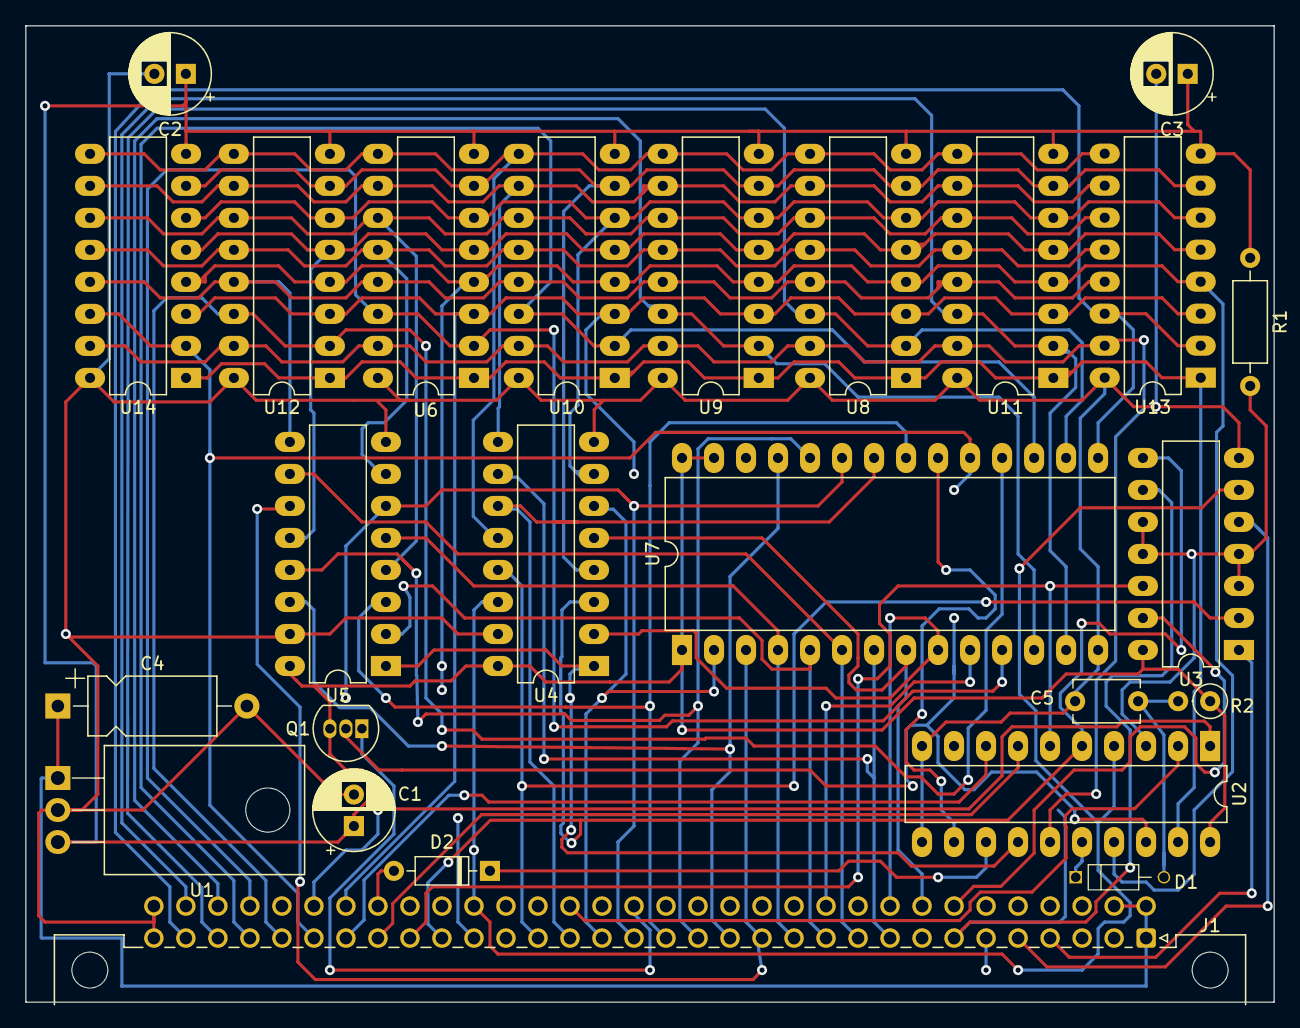
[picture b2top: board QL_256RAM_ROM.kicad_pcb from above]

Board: 2 copper layers, 99.1 x 77.5 mm, 25 parts (0 on the bottom side), 58 nets.

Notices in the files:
QL_256RAM_ROM/README.md:
CC BY-NC-SA 4.0
QL_Miracle_Trump_RAM/QL_Miracle_Trump_RAM.kicad_pcb:
(C) 2022 Alvaro Alea Fdz.
Under License
Licensed under Cern OHL-S
QL_Miracle_Trump_RAM/QL_Miracle_Trump_RAM.kicad_sch:
(C) 2026 Alvaro Alea Fdz
QL_external_ram_892Kb/QL_external_ram_892Kb.kicad_pcb:
(C) 2022-2026 Alvaro Alea Fdz
